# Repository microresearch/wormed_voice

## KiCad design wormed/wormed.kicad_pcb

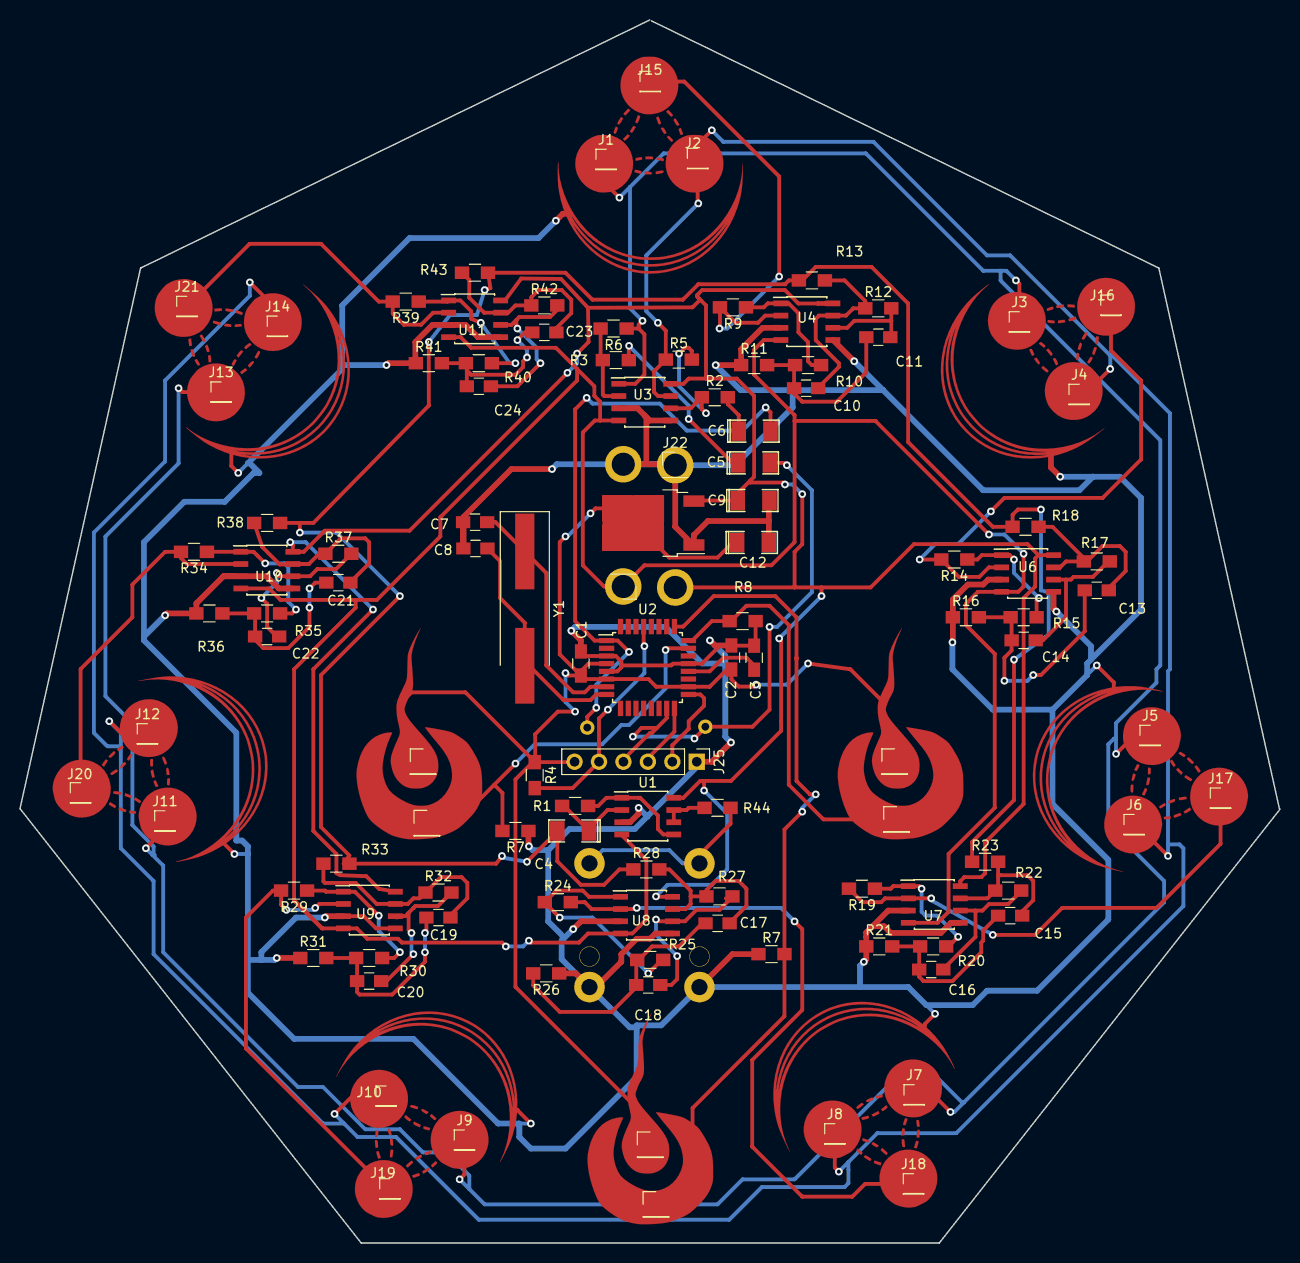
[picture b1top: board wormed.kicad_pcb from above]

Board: 2 copper layers, 130.9 x 127.1 mm, 103 parts (0 on the bottom side), 60 nets.

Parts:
C1, C2, C3: 100N; C_0805_HandSoldering
C4: 4u7; SMD-1206_Pol
C5, C6: 1uF; SMD-1206_Pol
C7, C8: 22pf; C_0805_HandSoldering
C9, C12: 10uF; SMD-1206_Pol
C10, C11: 22nF; C_0805_HandSoldering
C13, C14: 6n8; C_0805_HandSoldering
C15, C16, C17, C18, C19, C20, C23, C24: 2n2; C_0805_HandSoldering
C21, C22: 330pF; C_0805_HandSoldering
J1, J2, J3, J4, J5, J6, J7, J8, J9, J10, J11, J12, J13, J14, J15, J16, J17, J18, J19, J20, J21: Pin_Header_Straight_1x01_Pitch2.00mm
J22: Pin_Header_Straight_1x02_Pitch2.54mm
J25: Pin_Header_Straight_1x06_Pitch2.54mm
R1, R2, R3, R9, R13, R14, R18, R19, R23, R24, R28, R29, R33, R34, R38, R39, R43: 100K; R_0805_HandSoldering
R4: 10K; R_0805_HandSoldering
R5, R6, R17, R25: 1M; R_0805_HandSoldering
R7, R7#2, R8: 470K; R_0805_HandSoldering
R10: 200K; R_0805_HandSoldering
R11, R44: 1K; R_0805_HandSoldering
R12: 412K; R_0805_HandSoldering
R15: 523K; R_0805_HandSoldering
R16: 2.6K; R_0805_HandSoldering
R20: 1.2M; R_0805_HandSoldering
R21: 6K; R_0805_HandSoldering
R22: 2.4M; R_0805_HandSoldering
R26: 5K; R_0805_HandSoldering
R27: 2M; R_0805_HandSoldering
R30: 800K; R_0805_HandSoldering
R31: 4K; R_0805_HandSoldering
R32: 1.6M; R_0805_HandSoldering
R35: 3.2M; R_0805_HandSoldering
R36: 16K; R_0805_HandSoldering
R37: 6.5M; R_0805_HandSoldering
R40: 255K; R_0805_HandSoldering
R41: 1.6K; R_0805_HandSoldering
R42: 511K; R_0805_HandSoldering
U1, U3, U4, U6, U7, U8, U9, U10, U11: TL072; SOIC-8_3.9x4.9mm_Pitch1.27mm
U2: TQFP-32_7x7mm_Pitch0.8mm
Y1: Crystal; Crystal_SMD_HC49-SD_HandSoldering

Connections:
+5V: C1.2, C2.2, C12.1, J25.6, R4.1, U2.4, U2.6, U2.18
+BATT: C9.1, J22.2, U1.8, U3.8, U4.8, U6.8, U7.8, U8.8, U9.8, U10.8, U11.8
-BATT: U1.4, U3.4, U4.4, U6.4, U7.4, U8.4, U9.4, U10.4, U11.4
/ADC0: R7#2.2, U2.23
/ADC1: R8.2, U2.24
/GL: C6.2, U2.1
/GLOTTAL: J2.1, J4.1, J6.1, J8.1, J10.1, J12.1, J14.1, R5.1, U3.7
/IN0: J15.1, R9.2, U4.2
/IN1: J16.1, R14.2, U6.2
/IN2: J17.1, R19.2, U7.2
/IN3: J18.1, R24.2, U8.2
/IN4: J19.1, R29.2, U9.2
/IN5: J20.1, R34.2, U10.2
/IN6: J21.1, R39.2, U11.2
/NO: C5.2, J25.4, U2.15
/NOISE: J1.1, J3.1, J5.1, J7.1, J9.1, J11.1, J13.1, R6.1, U3.1
GND: C1.1, C2.1, C3.1, C7.1, C8.1, C9.2, C12.2, J22.1, J25.1, R7.1, R7#2.1, R8.1, R11.1, R16.1, R21.1, R26.1, R31.1, R36.1, R41.1, U1.3, U2.3, U2.5, U2.21, U3.3, U3.5, U4.3, U4.5, U6.3, U6.5, U7.3, U7.5, U8.3, U8.5, U9.3, U9.5, U10.3, U10.5, U11.3, U11.5
unnamed: C4.1, R1.2, U1.2
unnamed: C5.1, R3.2
unnamed: C6.1, R2.2
unnamed: C7.2, U2.7, Y1.1
unnamed: C8.2, U2.8, Y1.2
unnamed: C10.1, C11.1, R10.1, R11.2
unnamed: C10.2, R12.1, R13.2, U4.7
unnamed: C11.2, R12.2, U4.6
unnamed: C13.1, C14.1, R15.1, R16.2
unnamed: C13.2, R17.1, R18.2, U6.7
unnamed: C14.2, R17.2, U6.6
unnamed: C15.1, C16.1, R20.1, R21.2
unnamed: C15.2, R22.1, R23.2, U7.7
unnamed: C16.2, R22.2, U7.6
unnamed: C17.1, C18.1, R25.1, R26.2
unnamed: C17.2, R27.1, R28.2, U8.7
unnamed: C18.2, R27.2, U8.6
unnamed: C19.1, C20.1, R30.1, R31.2
unnamed: C19.2, R32.1, R33.2, U9.7
unnamed: C20.2, R32.2, U9.6
unnamed: C21.1, C22.1, R35.1, R36.2
unnamed: C21.2, R37.1, R38.2, U10.7
unnamed: C22.2, R37.2, U10.6
unnamed: C23.1, C24.1, R40.1, R41.2
unnamed: C23.2, R42.1, R43.2, U11.7
unnamed: C24.2, R42.2, U11.6
unnamed: J25.2, U2.17
unnamed: J25.3, U2.16
unnamed: J25.5, R4.2, U2.29
unnamed: R1.1, U1.1, U1.5
unnamed: R2.1, R5.2, U3.6
unnamed: R3.1, R6.2, U3.2
unnamed: R9.1, R10.2, U4.1
unnamed: R14.1, R15.2, U6.1
unnamed: R19.1, R20.2, U7.1
unnamed: R24.1, R25.2, U8.1
unnamed: R29.1, R30.2, U9.1
unnamed: R34.1, R35.2, U10.1
unnamed: R39.1, R40.2, U11.1
unnamed: R44.2, U1.6, U1.7
unnamed: C3.2, U2.20
unnamed: R7.2, U2.25
OUTPUT: C4.2, R13.1, R18.1, R23.1, R28.1, R33.1, R38.1, R43.1

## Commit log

2017-12-13 first for workshop
2017-12-13 workshop notes
2017-12-14 small correction for location
2019-02-18 new programmer
